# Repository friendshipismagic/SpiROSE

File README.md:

This is the default README, please edit me.

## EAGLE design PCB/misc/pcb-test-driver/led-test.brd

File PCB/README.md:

# Files

The final PCB are in the `Rotative_Base` and `LED_Panel` directories.

# Other

In `misc/`, you can find:

+ the EAGLE `pcb-test-driver/`, containing a useful PCB to test the LED drivers with some LED and multiplexing.
+ a `LED_Panel_4_layers` almost finished version with 4 layers (instead of 6) of the LED panel.

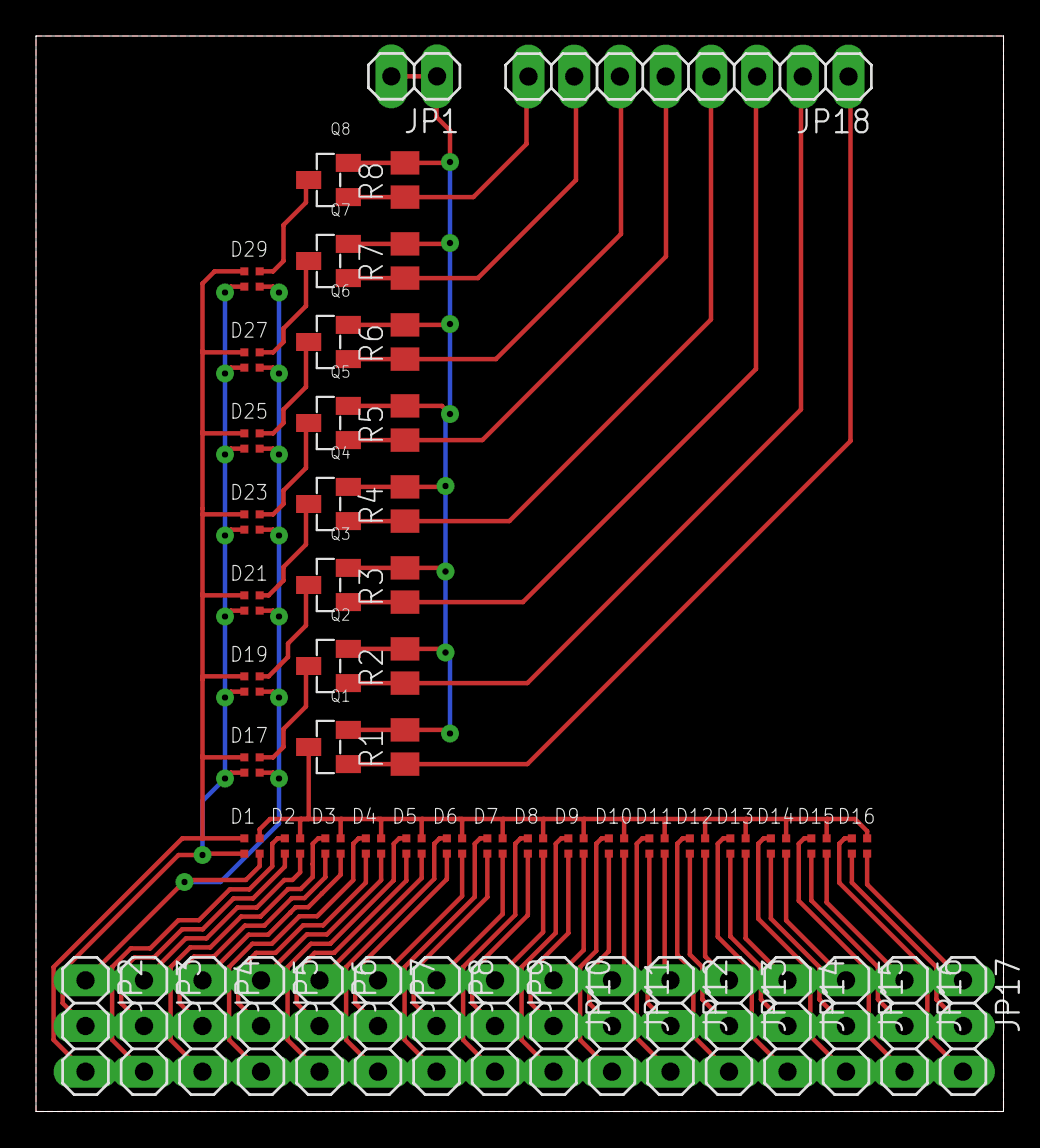
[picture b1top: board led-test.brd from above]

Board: 2 copper layers, 53.8 x 59.8 mm, 57 parts (0 on the bottom side), 65 nets.

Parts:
D1, D2, D3, D4, D5, D6, D7, D8, D9, D10, D11, D12, D13, D14, D15, D16, D17, D19, D21, D23, D25, D27, D29: LED3
JP1: 1X02
JP2, JP3, JP4, JP5, JP6, JP7, JP8, JP9, JP10, JP11, JP12, JP13, JP14, JP15, JP16, JP17: 1X03
JP18: 1X08
Q1, Q2, Q3, Q4, Q5, Q6, Q7, Q8: AO3401; SOT23-3
R1, R2, R3, R4, R5, R6, R7, R8: 100k; M0805

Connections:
+3V3: JP1.1, JP1.2, Q1.2, Q2.2, Q3.2, Q4.2, Q5.2, Q6.2, Q7.2, Q8.2, R1.2, R2.2, R3.2, R4.2, R5.2, R6.2, R7.2, R8.2
B0: D1.B, D17.B, D19.B, D21.B, D23.B, D25.B, D27.B, D29.B, JP2.3
B1: D2.B, JP3.3
B2: D3.B, JP4.3
B3: D4.B, JP5.3
B4: D5.B, JP6.3
B5: D6.B, JP7.3
B6: D7.B, JP8.3
B7: D8.B, JP9.3
B8: D9.B, JP10.3
B9: D10.B, JP11.3
B10: D11.B, JP12.3
B11: D12.B, JP13.3
B12: D13.B, JP14.3
B13: D14.B, JP15.3
B14: D15.B, JP16.3
B15: D16.B, JP17.3
G0: D1.G, D17.G, D19.G, D21.G, D23.G, D25.G, D27.G, D29.G, JP2.2
G1: D2.G, JP3.2
G2: D3.G, JP4.2
G3: D4.G, JP5.2
G4: D5.G, JP6.2
G5: D6.G, JP7.2
G6: D7.G, JP8.2
G7: D8.G, JP9.2
G8: D9.G, JP10.2
G9: D10.G, JP11.2
G10: D11.G, JP12.2
G11: D12.G, JP13.2
G12: D13.G, JP14.2
G13: D14.G, JP15.2
G14: D15.G, JP16.2
G15: D16.G, JP17.2
MUX0: JP18.1, Q1.1, R1.1
MUX1: JP18.2, Q2.1, R2.1
MUX2: JP18.3, Q3.1, R3.1
MUX3: JP18.4, Q4.1, R4.1
MUX4: JP18.5, Q5.1, R5.1
MUX5: JP18.6, Q6.1, R6.1
MUX6: JP18.7, Q7.1, R7.1
MUX7: JP18.8, Q8.1, R8.1
R0: D1.R, D17.R, D19.R, D21.R, D23.R, D25.R, D27.R, D29.R, JP2.1
R1: D2.R, JP3.1
R2: D3.R, JP4.1
R3: D4.R, JP5.1
R4: D5.R, JP6.1
R5: D6.R, JP7.1
R6: D7.R, JP8.1
R7: D8.R, JP9.1
R8: D9.R, JP10.1
R9: D10.R, JP11.1
R10: D11.R, JP12.1
R11: D12.R, JP13.1
R12: D13.R, JP14.1
R13: D14.R, JP15.1
R14: D15.R, JP16.1
R15: D16.R, JP17.1
VCC0: D1.VCC, D2.VCC, D3.VCC, D4.VCC, D5.VCC, D6.VCC, D7.VCC, D8.VCC, D9.VCC, D10.VCC, D11.VCC, D12.VCC, D13.VCC, D14.VCC, D15.VCC, D16.VCC, Q1.3
VCC1: D17.VCC, Q2.3
VCC2: D19.VCC, Q3.3
VCC3: D21.VCC, Q4.3
VCC4: D23.VCC, Q5.3
VCC5: D25.VCC, Q6.3
VCC6: D27.VCC, Q7.3
VCC7: D29.VCC, Q8.3

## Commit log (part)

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2018-01-22 Fix SPI MISO transmission
    - cmd_write must be captured when SS falls, not when it raises,
    as the command to which a response is sent is signaled when
    SS raises. There will be no clock cycle to prepare the response
    otherwise.
    - spi_clk ought to be ignored when SS is up. And when SS raises,
    out_reg and spi_miso can be returned to their respective reset
2018-01-22 FPGA/src/sync_sig.sv: add signal synchronization module
2018-01-22 Better SPI command decoding
    - Compute the number of bytes in the received command.
    - Return the old configuration when setting a new one.
    - Implement rotation data retrieval.
    - Check that an integral number of bytes has been received.
2018-01-22 FPGA/src/edges_detector.sv: add edges_detector module
2018-01-22 FPGA/src/spi_decoder.sv: add spi command decoder module
2018-01-22 FPGA/src/spi_iff.sv: change miso at negedge sck
2018-01-22 Fix include file name
2018-01-22 FPGA/quartus/memory-project: Add RAM block and timing constraints
2018-01-22 Change pin assignment
2018-01-22 FPGA/src/driver_controller: Update to match the new clock architecture
2018-01-22 FPGA/src/clk: add altera pll files
2018-01-22 Revert "FPGA/src/driver_controller: Update to match the new clock architecture"
    This reverts commit fd3897fc79f796a25cdebeeac4fe4fd2786c7da7.
2018-01-22 FPGA/src/clk: change frequancy to 66 MHz
2018-01-22 FPGA/lib/driver_cmd: fix lint issue
2018-01-22 FPGA/src/ remove edges_detector
2018-01-22 FPGA/quartus/ep3c40_rgb_pll: Change PLL parameters to fit the new clock design
2018-01-22 FPGA/quartus-de1soc/panel_test/: update pll value, remove unused files
2018-01-22 FPGA/quartus-de1soc/rgb_image_test: update pll value,remove unsued files
2018-01-22 Stay stuck in STALL unless we have a new config.
    At reset, a new configuration is available (the serialized one).
2018-01-22 FPGA/driver_controller: Update to newest clock architecture, update of the testbench
2018-01-22 FPGA/column_mux: Correction with respects to the unique clk at 66 MHz, overdrive timing correction
2018-01-23 FPGA/src: Remove clock_lse modules, Rename framebuffer clock
2018-01-23 FPGA/src/hall_sensor.sv: remove trailing whitespace
2018-01-23 FPGA/sim/column_mux: Remove clock_lse dependency from makefile
2018-01-23 FPGA/tb_src/systemc/tb_hall_sensor/: fix test
    storePositionSync and CheckPositionSync were'nt spawn at the right time.
    Add a second argument to sendHallSignals to choose the length of the
    second half turn. Try small and big speed variations.
    Give the sendHallSignals arguments to the CheckPositionSync method so it
    can compute the expected position_sync number.
2018-01-23 FPGA/tb_src/systemc/tb_hall_sensor: check the space between two position_sync
2018-01-23 FPGA/quartus/05_spi_test: add spi test project for EP3C40
2018-01-23 FPGA/src/SEG7_LUT.sv: move from hall_sensor_test project
2018-01-23 FPGA/quartus-de1soc/column_mux_test: clean project
2018-01-23 FPGA/src/ regenerate pll file to rename it clk_66
2018-01-23 FPGA/: remove clk files that shouldn't be here at all
2018-01-23 FPGA/quartus-de1soc/hall_sensor_test: clean project
2018-01-23 FPGA/quartus-de1soc/: add default nettype none in top module
2018-01-23 FPGA/quartus-de1soc/: rename panelx_test
2018-01-23 FPGA/quartus-de1soc/parallel_rgb_test/: clean project
2018-01-23 FPGA/quartus-de1soc/rgb_animation_test/: clean project
2018-01-23 FPGA/quartus-de1soc/parallel_rgb_test/: fix gpio declaration
2018-01-23 .gitlab-ci.yml: remove make install steps
2018-01-23 FPGA/quartus-de1soc/spi_test: clean project
2018-01-23 Add a get_speed command
2018-01-23 FPGA/quartus/rgb_pll: Change test point to rgb_clk
2018-01-23 FPGA/src/hall_sensor: Update module to ouptut the rotation speed on 16 bits
2018-01-23 FPGA/quartus: rename 05_spi_test
2018-01-24 tools/framer/Makefile: fix new path to libspirose
2018-01-24 lib: Fix `make install`
2018-01-24 framer: Fix CI
2018-01-24 Output data from the FPGA in an easily parsable way
2018-01-24 FPAG/src/: replace counter logic declaration with integer
2018-01-24 FPGA/quartus-de1soc/caterpillar_animation: cleanup project
2018-01-24 FPGA/src/heartbeat: add heartbeat module
2018-01-24 ci: Run renderer-poc tests in test step
2018-01-24 FPGA/quartus/hall_sensor_test: Add test structure
2018-01-24 FPGA/quartus/single_led: Fix module inputs and tcl files in qsf
2018-01-24 FPGA/quartus/hall_sensor: Fix the included tcl files in project
2018-01-24 FPGA/quartus/single_led: Use default configuration in the svh file
2018-01-24 FPGA/quartus/memory: Change the input clock to the rgb clock
2018-01-24 FPGA/src/: add ram_dual_port files
2018-01-24 FPGA/quartus/hall_sensor: Change to new notations for driver pin assignment
2018-01-24 CHange PLL to use 21MHz instead of 27MHz
2018-01-24 Add TCL of pin assignments to main tcl
2018-01-24 Add PT_26, PT_23, PT_24 to assignments
2018-01-24 FPGA/quartus/memory_test: replace ram with dual port and clock
2018-01-24 Correct top module and add timing assignments
2018-01-24 PLL and Top module cleanup for 5 first tests
2018-01-24 Correct timing constraints
2018-01-24 FPGA/quartus/single_led: Add new_configuration_ready signal
2018-01-24 FPGA/quartus/hall_sensor: Add driving of new_configuration_ready to get out of the STREAM state of driver controller
2018-01-24 Simplify memory test
2018-01-24 fpga/tests: Add RGB test
2018-01-24 fpga/rgb_test: Fix build
2018-01-24 FPGA/quartus/hall_sensor: Add reset synchronized on locked
2018-01-24 FPGA/quartus/single_led: Use of correct top module for the test
2018-01-24 FPGA/quartus/caterpillar_test: add project
2018-01-24 FPGA/quartus/single_led: Fix for signals
2018-01-24 FPGA/quartus/hall_sensor: Use of the topmodule template, assignment of *_a and *_b singals altogether
2018-01-24 FPGA/quartus/single_led: Rework of the test number
2018-01-25 Add LUT
2018-01-25 FPGA/quartus/hall_sensor: Change test number
2018-01-25 FPGA/src/framebuffer: fix sync between framebuffer adn driver_controller
2018-01-25 FPGA/quartus/09_column_mux/: rename project, add driver lut
2018-01-25 FPGA/quartus/10_single_led/: fix ram_data value
2018-01-25 Fix error in Makefile
2018-01-25 Fix typos, add default_nettype none to test 09
2018-01-25 FPGA/src/framebuffer: Fix the way the data is output relatively to the clokc_enable signal
2018-01-25 tools/spi_cli: use match construct instead of if let
2018-01-26 tools/spi_cli: add disable_mux command
2018-01-26 tools/spi_cli: add send_driver_data command
2018-01-26 FPGA/spi: Add driver data command to spi parser
2018-01-26 New version of driver controller
2018-01-26 Add comb signals with resync
2018-01-26 Add new states SCLK
2018-01-26 Remove inter-dependent signals
2018-01-26 FPGA/src/driver_controller: fix missing state transition
2018-01-26 Add yocto linux conf
2018-01-26 FPGA/src/spi_decoder.sv: zero the mux and data by default
2018-01-26 tools/spi_cli: document possible settings of several muxes
    fix #91
2018-01-26 PCB/LED_panel: update resistor value
2018-01-26 FPGA/quartus/12_spi_display: fix project
2018-01-26 FPGA/src/ separate driver_controller from the one used in spi demo
2018-01-26 fpga/quartus: Add all tests to makefile
2018-01-26 FPGA/quartus/09_column_mux: remove sout in driver_controller
2018-01-26 Bugfix: include right driver_controller (with spi)
2018-01-26 Change LUTs order
2018-01-26 Bugfix: remove ambiguous caterpillar.qsf name
2018-01-27 FPGA/src/driver_controller_spi_driver: fix lut for 3rd driver line
2018-01-27 FPGA/src/framebuffer.sv: update to send data by 48 bit packet
    The new driver_contreoller module now require 48 bit packet when sending
    driver ready, corresponding to a bit of each led (or to speak in terms
    of lat command, one WRTGS). After 9 driver_ready (8 WRTGS plus 1 LATGS)
    we swap the buffers.
2018-01-28 FPGA/src/framebuffer.sv: fix counters
2018-01-28 FPGA/src: fix driver_ready sent 9 times instead of 8
2018-01-29 FPGA/src/framebuffer.sv: fix missing column_ready in slice_cnt increment
2018-01-29 FPGA/src/framebuffer.sv: change ram_addr computation
2018-01-29 FPGA/src/: send gclk continuously
2018-01-29 Add send_driver spi_cli command to send full data to drivers
2018-01-29 FPGA: Disable tests before rework
2018-01-29 Rename signals from SPI
2018-01-29 FPGA/src/color_lut: add module to shuffle bits according to the colorlut
2018-01-29 Fix 12_spi_display compilation errors
2018-01-30 Fix space in cli.yml, hiding the release cmd
2018-01-30 FPGA/src/driver_controller.sv: send gclk only after config and first latgs
2018-01-30 FPGA/src/: test driver_controller with spi, add lut
2018-01-30 FPGA/src/driver_controller.sv: add TMGRST, LINEREST, and allow to resend config
2018-01-30 Remove unused files to avoid confusion
2018-01-30 Add ram from mega wizard
2018-01-30 tools/spi_cli: update rgb_logic to send rgb data
2018-01-30 Update RAM size, add RAM blocks instanciation
2018-01-30 spi_decoder: Add command to override driver LUT
2018-01-30 Dont hardcode quartus_sh path
2018-01-30 Fix incorrect pin assignment
2018-01-30 Remove last byte sent by error on send_driver_rgb
2018-01-30 Rename poker module
2018-01-30 Add right poker formatter
2018-01-30 ALWAYS REMOVE LGSE*, PLZ
2018-01-30 Factorize sending data from a file
2018-01-30 Trace SPI device opening in verbose mode
2018-01-30 Be stricter in cli.yml file
2018-01-30 FPGA/src/driver_controller: fix deadlock when reconfiguring
2018-01-30 Add reset command in spi_cli
2018-01-30 WIP: Enable driver_controller test and fix binding
2018-01-30 Fix FPGA lint errors and remove ram
2018-01-30 ram_lru: Switch read_data to output
2018-01-30 FPGA/src/framebuffer.sv: update to new LRU arch
2018-01-30 Implement read_pixel and write_pixel commands
2018-01-30 Cleanup
2018-01-30 Remove clock switch-over to hold timing requirements
2018-01-30 Add color command
2018-01-30 ram_lru: Add write_done input signal and behave like a real RAM
2018-01-30 ram_lru: Replace tabs with spaces
2018-01-30 Remove unused RAM
2018-01-30 Add RAM+framebuffer in top module, fix address width
2018-01-31 FPGA/src: fix memory manipulation with spi
2018-01-31 FPGA/src/ram_line_writer.sv: add ram_line_writer for spi
2018-01-31 FPGA/quartus/12_spi_display: add ram_line_writer
2018-01-31 Remove send_driver_data command
2018-01-31 Better error messages
2018-01-31 Rename COMMANDS to something meaningful
2018-01-31 FPGA/src/framebuffer: wait one cycle more for the ram_data
2018-01-31 Use only 7 lower bits of mux_cnt
2018-01-31 Set default SPI speed to 14Mbps
2018-01-31 Remove unnecessary Clone derivation
2018-01-31 Style
2018-01-31 tools/spi_cli: add command to debug framebuffer
2018-01-31 FPGA/src/spi_decoder: fix multiple driver column and add fb profiling commands
2018-01-31 Better get_speed command
2018-01-31 FPGA/src/hall_sensor: Change speed_data in hall_sensor
2018-01-31 Fix mirroring issue
2018-01-31 Add Spi_SOL in 15_RAM
2018-01-31 Bugfix: use pixel_data and ram addr
2018-01-31 Mirror ublock outputs
2018-01-31 Add 15 instances of RAM+fb+poker_formatter
2018-01-31 ram_lru/CI: Fix lint step
2018-01-31 WIP: test code for hall sensor
2018-01-31 docs: Add hall effect sensor datasheet
2018-01-31 Add hall sensor counter
2018-01-31 Rewrite hall pll
2018-01-31 Fix off by one minor error
2018-01-31 Fix off by 2 errors
2018-01-31 Set SPI speed to 5MHz by default
2018-01-31 rgb_display: Add Quartus-generated FIFO
2018-01-31 sync_sig: Fix reset value for signals wider than one bit
2018-01-31 rgb_display: Instanciate rgb_logic
2018-01-31 rgb_display: Connect RGB to RAM module
2018-01-31 rgb_display: Name muxed signals
2018-01-31 rgb_logic: Fix off-by-one error and swap R and B
2018-01-31 rgb_display: Resize pixel line and column signals
2018-01-31 rgb_display: Use FIFO to sync RGB
2018-02-01 tools/spi_cli: add manage option command
2018-02-01 rgb_display: Fix one-column offset
2018-02-01 rgb_display: Use hall sensors
2018-02-01 FPGA/src/ram_15: Fix module signals
2018-02-01 FPGA/: try to fix synchro
2018-02-01 FPGA/src/ram_fifo.sv: fix full signal
2018-02-01 Add no_write condition in internal ram
2018-02-01 FPGA/src/ram_fifo.sv: fix signal size
2018-02-02 FPGA/src/rgb_logic.sv: fix EOS sending
2018-02-02 Fix comment: we have 128 slices
2018-02-02 FPGA/src/ram_fifo.sv: fix can_write condition
2018-02-02 Prevent useless warnings and deny warnings
2018-05-15 Add copyright notice
2018-10-27 Reformat
